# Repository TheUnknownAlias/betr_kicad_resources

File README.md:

# KiCad Component Library

This repository contains shared KiCad symbols and footprints for our projects.

## Structure
- `symbols/`: Contains schematic symbol libraries (.lib files)
- `footprints/`: Contains footprint libraries (.pretty folders)
- `3dmodels/`: Optional 3D models for components

## Usage
1. Clone this repository
2. In KiCad:
  - For symbols: Preferences → Manage Symbol Libraries → Add path to .lib files
  - For footprints: Preferences → Manage Footprint Libraries → Add path to .pretty folders

## Contributing
Please follow our contribution guidelines when adding new components.

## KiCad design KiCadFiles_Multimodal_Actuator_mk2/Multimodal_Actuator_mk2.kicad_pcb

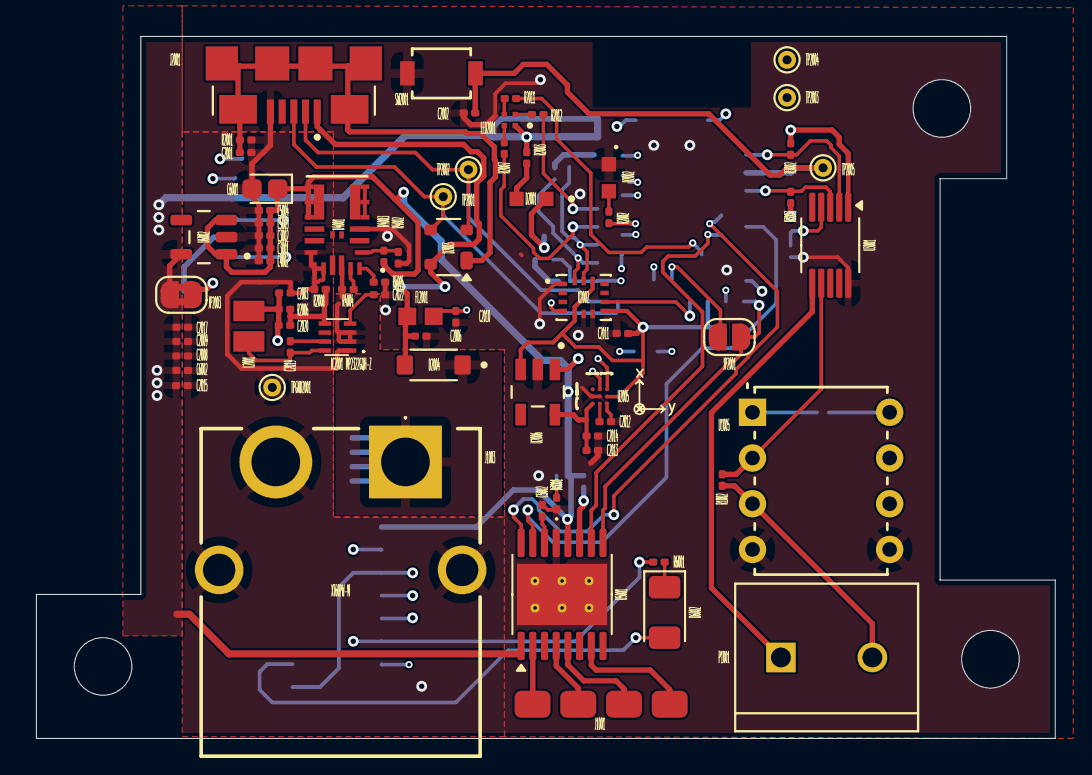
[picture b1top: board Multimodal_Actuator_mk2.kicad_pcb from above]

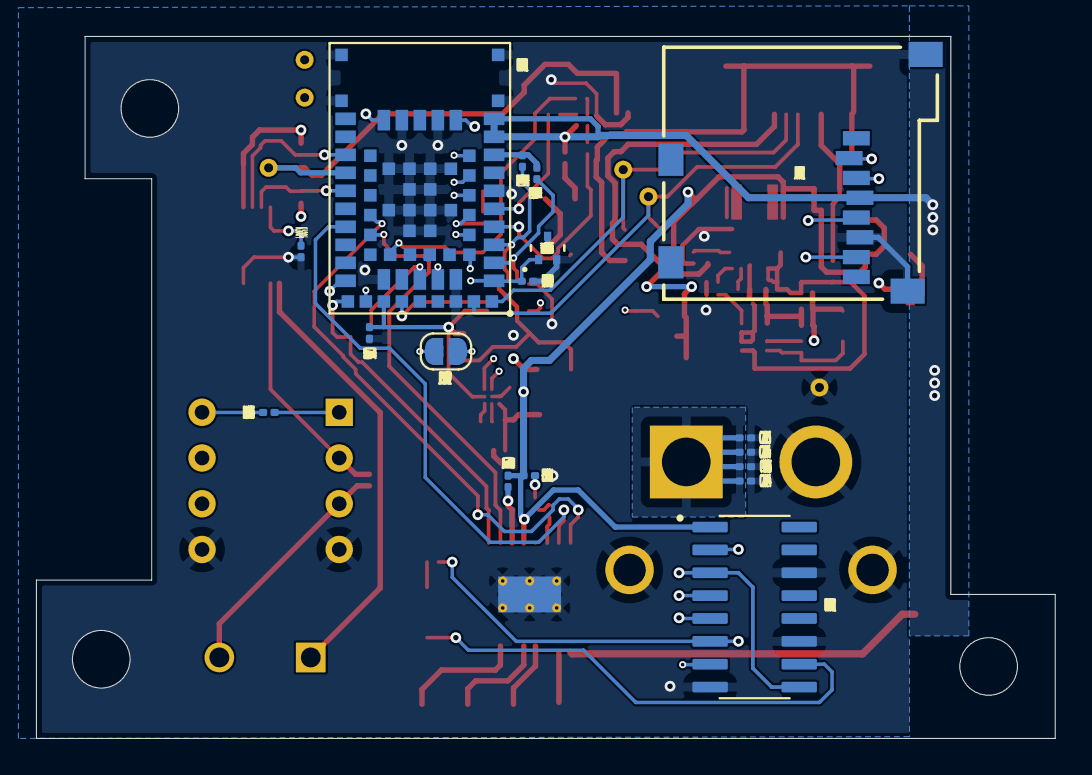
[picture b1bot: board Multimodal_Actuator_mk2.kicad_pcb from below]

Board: 4 copper layers, 56.6 x 39.0 mm, 91 parts (17 on the bottom side), 71 nets.

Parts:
C2001: 4.7 nF; C_0201_0603Metric
C2002, C2005, C2008, C2009, C2011, C2013: 100 nF; C_0201_0603Metric
C2003, C2017: 10 μF; C_0201_0603Metric
C2004, C2023: 10 μF 25V; C_0201_0603Metric
C2006, C2010: 1 nF; C_0201_0603Metric
C2012: 2.2uF; C_0201_0603Metric
C2014, C2015: 1uF; C_0201_0603Metric
C2019, C2024: 100 nF 50V; C_0201_0603Metric
C2020: 22 nF; C_0201_0603Metric
C2022: 1 μF; C_0201_0603Metric
C3001: 0.1uF; C_0201_0603Metric
C3002: 10uF; C_0201_0603Metric
C4002: 22μF; C_0201_0603Metric
C4003, C5002: 10μF; C_0201_0603Metric
C5001: 0.1μF; C_0201_0603Metric
C5003, C5004: 10μF/16V; C_0201_0603Metric
C6001: 100nF; CP_EIA-1608-08_AVX-J
C6002: 100nF; C_0201_0603Metric
D2001: APT1608YC; LED_APT1608YC
D2002: HSMG-C190
D2003: PRTR5V0U2X; SOT-143
D2004: PMEG6020AELRX; SODFL3517X110N
D3001: Green LED; LED_0201_0603Metric
D6002: LTST-C150EKT(RED_LED); LED_1206_3216Metric
FL2001: BLM18EG101TN1D; BEADC1608X65N
H1001, H1002, H1003: MountingHole; MountingHole_3.2mm_M3
IC2001: MP2322GQH-Z; MP2322GQHZ
J1001: Conn_01x04_Socket; 01x04_SMD_Connector_Linear
J1003: XT60PW-M; XT60PWM
J2001: ZX62-AB-5PA_31_; HIROSE_ZX62-AB-5PA_31_
J6001: 2908-05WB-MG; 3M_2908-05WB-MG
JP2001, JP2002: SolderJumper_2_Open; SolderJumper-2_P1.3mm_Open_RoundedPad1.0x1.5mm
JP2003: SolderJumper_2_Bridged; SolderJumper-2_P1.3mm_Bridged2Bar_RoundedPad1.0x1.5mm
L2001: MAKK2016T3R3M; INDC2016X100N
LED2001: SMLP34RGBN1W3; SMLP34_ROM
P1001: 282837-2; TE_282837-2
R1002: 100; R_0201_0603Metric
R1003: 1.2k; R_0201_0603Metric
R2001: 1M; R_0201_0603Metric
R2002, R2003: 330; R_0201_0603Metric
R2006, R2009, R2013, R2014: 976k; R_0201_0603Metric
R2007, R2011, R2012, R6001: 1k; R_0201_0603Metric
R2008: 220k; R_0201_0603Metric
R3001, R3002, R3003, R3004: 4.7kohm; R_0201_0603Metric
R4002: 19.1k; R_0201_0603Metric
R4003, R4004: 100k; R_0201_0603Metric
R4005: 53.6k; R_0201_0603Metric
SW2001: B3U-1000PM; B3U-1000PM_OMR
TP2001: D+; TestPoint_THTPad_D1.0mm_Drill0.5mm
TP2002: D-; TestPoint_THTPad_D1.0mm_Drill0.5mm
TP2003: SWDCLK; TestPoint_THTPad_D1.0mm_Drill0.5mm
TP2004: SWDIO; TestPoint_THTPad_D1.0mm_Drill0.5mm
TP2005: RESET; TestPoint_THTPad_D1.0mm_Drill0.5mm
TPGND2001: GND; TestPoint_THTPad_D1.0mm_Drill0.5mm
U1005: AD623ANZ; N_8_ADI
U2001: NINA-B306-00B; XCVR_NINA-B306-00B
U2002: BMI270; XDCR_BMI270
U2004: 2N7002T-7-F; SOT523_2N7002T_DIO
U2005: BMM350; BGA9_BMM350_BOS
U2006: TPS7A2018PDBVR; SOT95P280X145-5N
U3001: MCP4728; MSOP-10_3x3mm_P0.5mm
U4001: MPM3610GQV-P; QFN3p0x5p0x1p6_MPM3610_MNP
U5001: DRV8833PWP; HTSSOP-16-1EP_4.4x5mm_P0.65mm_EP3.4x5mm_Mask2.46x2.31mm_The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
U6001: CD74HC4050M96; SOIC127P600X175-16N
U6002: LP2985-33DBVR; SOT95P280X145-5N

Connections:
+3.3V: C2008.1, C2009.1, C2015.1, C2017.2, C6002.1, J6001.4 (VDD), JP2003.2 (B), LED2001.1, R2003.1, U2001.9 (VCC_IO), U2001.10 (VCC), U2006.1 (IN), U5001.1 (~SLEEP), U6002.5 (VOUT)
/AIN1: U2001.40 (GPIO_40), U5001.16 (AIN1)
/AIN2: U2001.22 (GPIO_22), U5001.15 (AIN2)
/Arduino_nano_Rev2/1.8VOUT: C2013.1, C2014.1, U2005.C1 (VDD), U2006.5 (OUT)
/Arduino_nano_Rev2/BMI270_INT1: U2001.32 (TRACE_D2/GPIO_32), U2002.4 (INT1)
/Arduino_nano_Rev2/BMI270_INT2: U2001.50 (QSPI_D0/GPIO_50), U2002.9 (INT2)
/Arduino_nano_Rev2/D8: JP2002.2 (B), U2001.48 (QSPI_D1/GPIO_48)
/Arduino_nano_Rev2/LB: R2011.2, U2001.43 (GPIO_43)
/Arduino_nano_Rev2/LG: R2007.2, U2001.4 (GPIO_4)
/Arduino_nano_Rev2/LR: R2012.2, U2001.5 (GPIO_5)
/Arduino_nano_Rev2/RESETN: C2002.1, SW2001.2, TP2005.1, U2001.19 (~RESET)
/Arduino_nano_Rev2/R_PULLUP: R2013.1, R2014.1, U2001.8 (SWO/TRACE_D0/GPIO_8)
/Arduino_nano_Rev2/SCL1: R2013.2, U2001.3 (GPIO_3), U2002.13 (SCX), U2005.A3 (SCK)
/Arduino_nano_Rev2/SDA1: R2014.2, U2001.2 (GPIO_2), U2002.14 (SDX), U2005.A2 (SDA)
/Arduino_nano_Rev2/USB_SHIELD: C2001.2, D2003.1 (GND), J2001.S1 (SHIELD), J2001.S2 (SHIELD__1), J2001.S3 (SHIELD__2), J2001.S4 (SHIELD__3), J2001.S5 (SHIELD__4), J2001.S6 (SHIELD__5), R2001.1
/BIN1: JP2001.2 (B), U2001.47 (QSPI_D3/GPIO_47), U5001.9 (BIN1)
/BIN2: U2001.41 (GPIO_41), U5001.10 (BIN2)
/CLK: R2009.1, U2001.1 (GPIO_1), U2004.1 (G), U6001.3 (1A), U6001.9 (4A)
/CS: U2001.36 (GPIO_36), U6001.7 (3A)
/DI: U2001.35 (GPIO_35), U6001.5 (2A)
/DO: J6001.7 (DATA_OUT), U2001.34 (GPIO_34)
/DRV8833/AOUT1: J1001.1, U5001.2 (AOUT1)
/DRV8833/AOUT2: J1001.2, U5001.4 (AOUT2)
/DRV8833/BOUT1: J1001.3, U5001.7 (BOUT1)
/DRV8833/BOUT2: J1001.4, U5001.5 (BOUT2)
/InAmpOutput: U1005.6 (OUTPUT), U2001.25 (GPIO_25)
/MCP4728_Quad_DAC/LDAC: R3004.2, U3001.4 (~LDAC)
/MPM3610_5V_Buck/EN: R4004.1, U4001.17 (EN)
/SCL: R3002.2, U2001.18 (GPIO_18), U3001.2 (SCL)
/SDA: R3003.2, U2001.20 (GPIO_20), U3001.3 (SDA)
/VA: P1001.1, U3001.6 (VOUTA)
/VB: R1002.2, U1005.2 (-IN), U3001.7 (VOUTB)
GND: C2001.1, C2002.2, C2003.1, C2004.2, C2005.1, C2006.2, C2008.2, C2009.2, C2010.2, C2011.2, C2012.1, C2013.2, C2014.2, C2015.2, C2017.1, C2022.2, C2023.2, C2024.2, C3001.2, C3002.2, C4002.2, C4003.2, C5002.2, C5003.2, C5004.2, C6001.2, C6002.2, D2002.C, D3001.1 (K), IC2001.1 (GND), J1003.2, J1003.3 (MH1), J1003.4 (MH2), J2001.5 (GND), J6001.6 (VSS), J6001.9 (GND), J6001.10 (GND), R2001.2, R2008.2, R2009.2, R3004.1, R4002.2, R4005.1, SW2001.1, TPGND2001.1, U1005.4 (-VS), U1005.5 (REF), U2001.6 (GND), U2001.12 (GND__1), U2001.14 (GND__2), U2001.26 (GND__3), U2001.30 (GND__4), U2001.53 (GND__5), U2001.EAGP1 (EAGP), U2001.EAGP2 (EAGP__1), U2001.EAGP3 (EAGP__2), U2001.EAGP4 (EAGP__3), U2001.EGP1 (EGP), U2001.EGP2 (EGP__1), U2001.EGP3 (EGP__2), U2001.EGP4 (EGP__3), U2001.EGP5 (EGP__4), U2001.EGP6 (EGP__5), U2001.EGP7 (EGP__6), U2001.EGP8 (EGP__7), U2001.EGP9 (EGP__8), U2001.EGP10 (EGP__9), U2001.EGP11 (EGP__10), U2001.EGP12 (EGP__11), U2002.1 (SDO), U2002.6 (GNDIO), U2002.7 (GND), U2004.2 (S), U2005.B1 (GND), U2005.B2 (ADSEL), U2005.C3 (BYPASS), U2006.2 (GND), U3001.10 (VSS), U4001.3 (AGND), U4001.12 (PGND), U4001.13 (PGND), U4001.14 (PGND), U5001.13 (GND), U5001.17 (GND), U6001.8 (GND), U6001.11 (5A), U6001.14 (6A), U6002.2 (GND)
unnamed: D2001.2, R2003.2
unnamed: D2002.A, R2002.2
unnamed: D2003.2 (I/O1), J2001.2 (D-), TP2002.1, U2001.55 (USB_DM)
unnamed: D2003.3 (I/O2), J2001.3 (D+), TP2001.1, U2001.54 (USB_DP)
unnamed: D3001.2 (A), R3001.2
unnamed: D6002.2 (A), U6001.10 (4Y)
unnamed: D6002.1 (K), R6001.1
unnamed: C2019.2, IC2001.7 (BST)
unnamed: C2020.2, IC2001.5 (FB), R2006.1, R2008.1
unnamed: C2019.1, IC2001.8 (SW), L2001.2
unnamed: C2022.1, IC2001.4 (VCC)
unnamed: J6001.2 (CS), R6001.2, U6001.6 (3Y)
unnamed: J6001.3 (DATA_IN), U6001.4 (2Y)
unnamed: J6001.5 (SCLK), U6001.2 (1Y)
unnamed: JP2001.1 (A), U2001.28 (NFC1/GPIO_28)
unnamed: JP2002.1 (A), U2001.29 (NFC2/GPIO_29)
unnamed: C2003.2, C2020.1, JP2003.1 (A), L2001.1, R2006.2
unnamed: LED2001.2, R2012.1
unnamed: LED2001.3, R2011.1
unnamed: LED2001.4, R2007.1
unnamed: P1001.2, R1002.1, U1005.3 (+IN)
unnamed: R1003.2, U1005.8 (+RG)
unnamed: R1003.1, U1005.1 (-RG)
unnamed: TP2003.1, U2001.11 (SWDCLK)
unnamed: TP2004.1, U2001.15 (SWDIO)
unnamed: R2002.1, U2001.33 (TRACE_D3/GPIO_33)
unnamed: C2010.1, FL2001.2, U2001.31 (VBUS)
unnamed: D2001.1, U2004.3 (D)
unnamed: C2012.2, U2005.C2 (CRST)
unnamed: R4005.2, U4001.18 (AAM)
unnamed: R4002.1, R4003.2, U4001.1 (FB)
unnamed: U4001.4 (SW), U4001.5 (SW), U4001.6 (SW)
unnamed: C5001.1, U5001.11 (VCP)
unnamed: C5002.1, U5001.14 (VINT)
VCC: C3001.1, C3002.1, C4002.1, C5001.2, C5003.1, C5004.1, C6001.1, R3001.1, R3002.1, R3003.1, R4003.1, U1005.7 (+VS), U3001.1 (VDD), U4001.7 (OUT), U4001.8 (OUT), U4001.9 (OUT), U5001.12 (VM), U6001.1 (VCC), U6002.1 (VIN), U6002.3 (ON/~OFF)
VDD_ENV: C2005.2, C2011.1, U2001.49 (QSPI_D2/GPIO_49), U2002.5 (VDDIO), U2002.8 (VDD), U2002.12 (CSB), U2005.B3 (VDDIO), U2006.3 (EN)
VUSB: C2006.1, D2003.4 (VCC), D2004.A, FL2001.1, J2001.1 (VCC)
Vin: C2004.1, C2023.1, C2024.1, C4003.1, D2004.C, IC2001.2 (IN), IC2001.3 (EN), J1003.1, R4004.2, U4001.16 (IN)

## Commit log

2025-08-05 General structure
2025-09-09 All custom files for kicad
2025-09-09 KiCadFiles
